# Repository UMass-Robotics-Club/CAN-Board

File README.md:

# CAN Board

Features:
* 6 CAN lines
* [RP2040](https://datasheets.raspberrypi.com/rp2040/rp2040-datasheet.pdf) microcontroller
* 16MB flash
* Many Interfaces
    * USB-C
    * UART
    * SPI
    * GPIO
* SWD debugging

This board has 6 independent CAN lines driven by 6 [MCP251863T-E/9PX](https://ww1.microchip.com/downloads/aemDocuments/documents/APID/ProductDocuments/DataSheets/MCP251863-External-CAN-FD-Controller-with-Integrated-Transceiver-DS20006624.pdf) CAN controllers. Each CAN controller is interfaced with the central microcontroller through an internal SPI bus along with 2 interrupt pins for general purpose and RX interrupts. There is also a STBY pin for the CAN transceiver that is connected to the XSTBY pin on the CAN controller.

## RP2040 Pinout
| GPIO | Function |
|------|----------|
| 0 | UART TX | 
| 1 | UART RX |
| 2 | SPI0 SCK |
| 3 | SPI0 TX |
| 4 | SPI0 RX |
| 5 | SPI0 CS 1 |
| 6 | SPI0 CS 2 |
| 7 | SPI0 CS 3 |
| 8 | SPI0 CS 4 |
| 9 | SPI0 CS 5 |
| 10 | SPI0 CS 6 |
| 11 | SPI1 TX |
| 12 | SPI1 RX |
| 13 | SPI1 CS |
| 14 | SPI1 SCK |
| 15 | GPIO pin 1 |
| 16 | CAN6 RX INT |
| 17 | CAN6 INT |
| 18 | CAN5 RX INT |
| 19 | CAN5 INT |
| 20 | CAN4 RX INT |
| 21 | CAN4 INT |
| 22 | CAN3 RX INT |
| 23 | CAN3 INT |
| 24 | CAN2 RX INT |
| 25 | CAN2 INT |
| 26 | GPIO pin 2 |
| 27 | GPIO pin 3 |
| 28 | CAN1 RX INT |
| 29 | CAN1 INT |

Notes:
* `SPI0` is the internal SPI bus which connects to the CAN controllers with `SPI0 CS X` being the chip select for CAN controller X.
* `SPI1` is the SPI bus exposed over the SPI connector.
* `GPIO 15 (GPIO pin 1)` is attached to a mosfet and LED as an indicator and therefore should have pull down enabled if being used as an input.
* `GPIO 26 & 27 (GPIO pin 26 & 27)` can be used an analog inputs.
* `CANX INT` is a general purpose interrupt pin for CAN controller X that will trigger when any interrupt in the CAN controller is triggered. This pin is inverted (active LOW).
* `CANX RX INT` is configurable to trigger when CAN controller X's RX interrupt is triggered. As an interrupt, this pin is inverted (active LOW).

## Project Structure
* `CAD`: The kiCAD project (PCB/schematics)
    * `Components`: Imported components each in their own folder
* `code`: Firmware for the microcontroller in a pretty standard C project structure
    * `include`: Header files
    * `src`: C/C++ files
* `images`: All the images

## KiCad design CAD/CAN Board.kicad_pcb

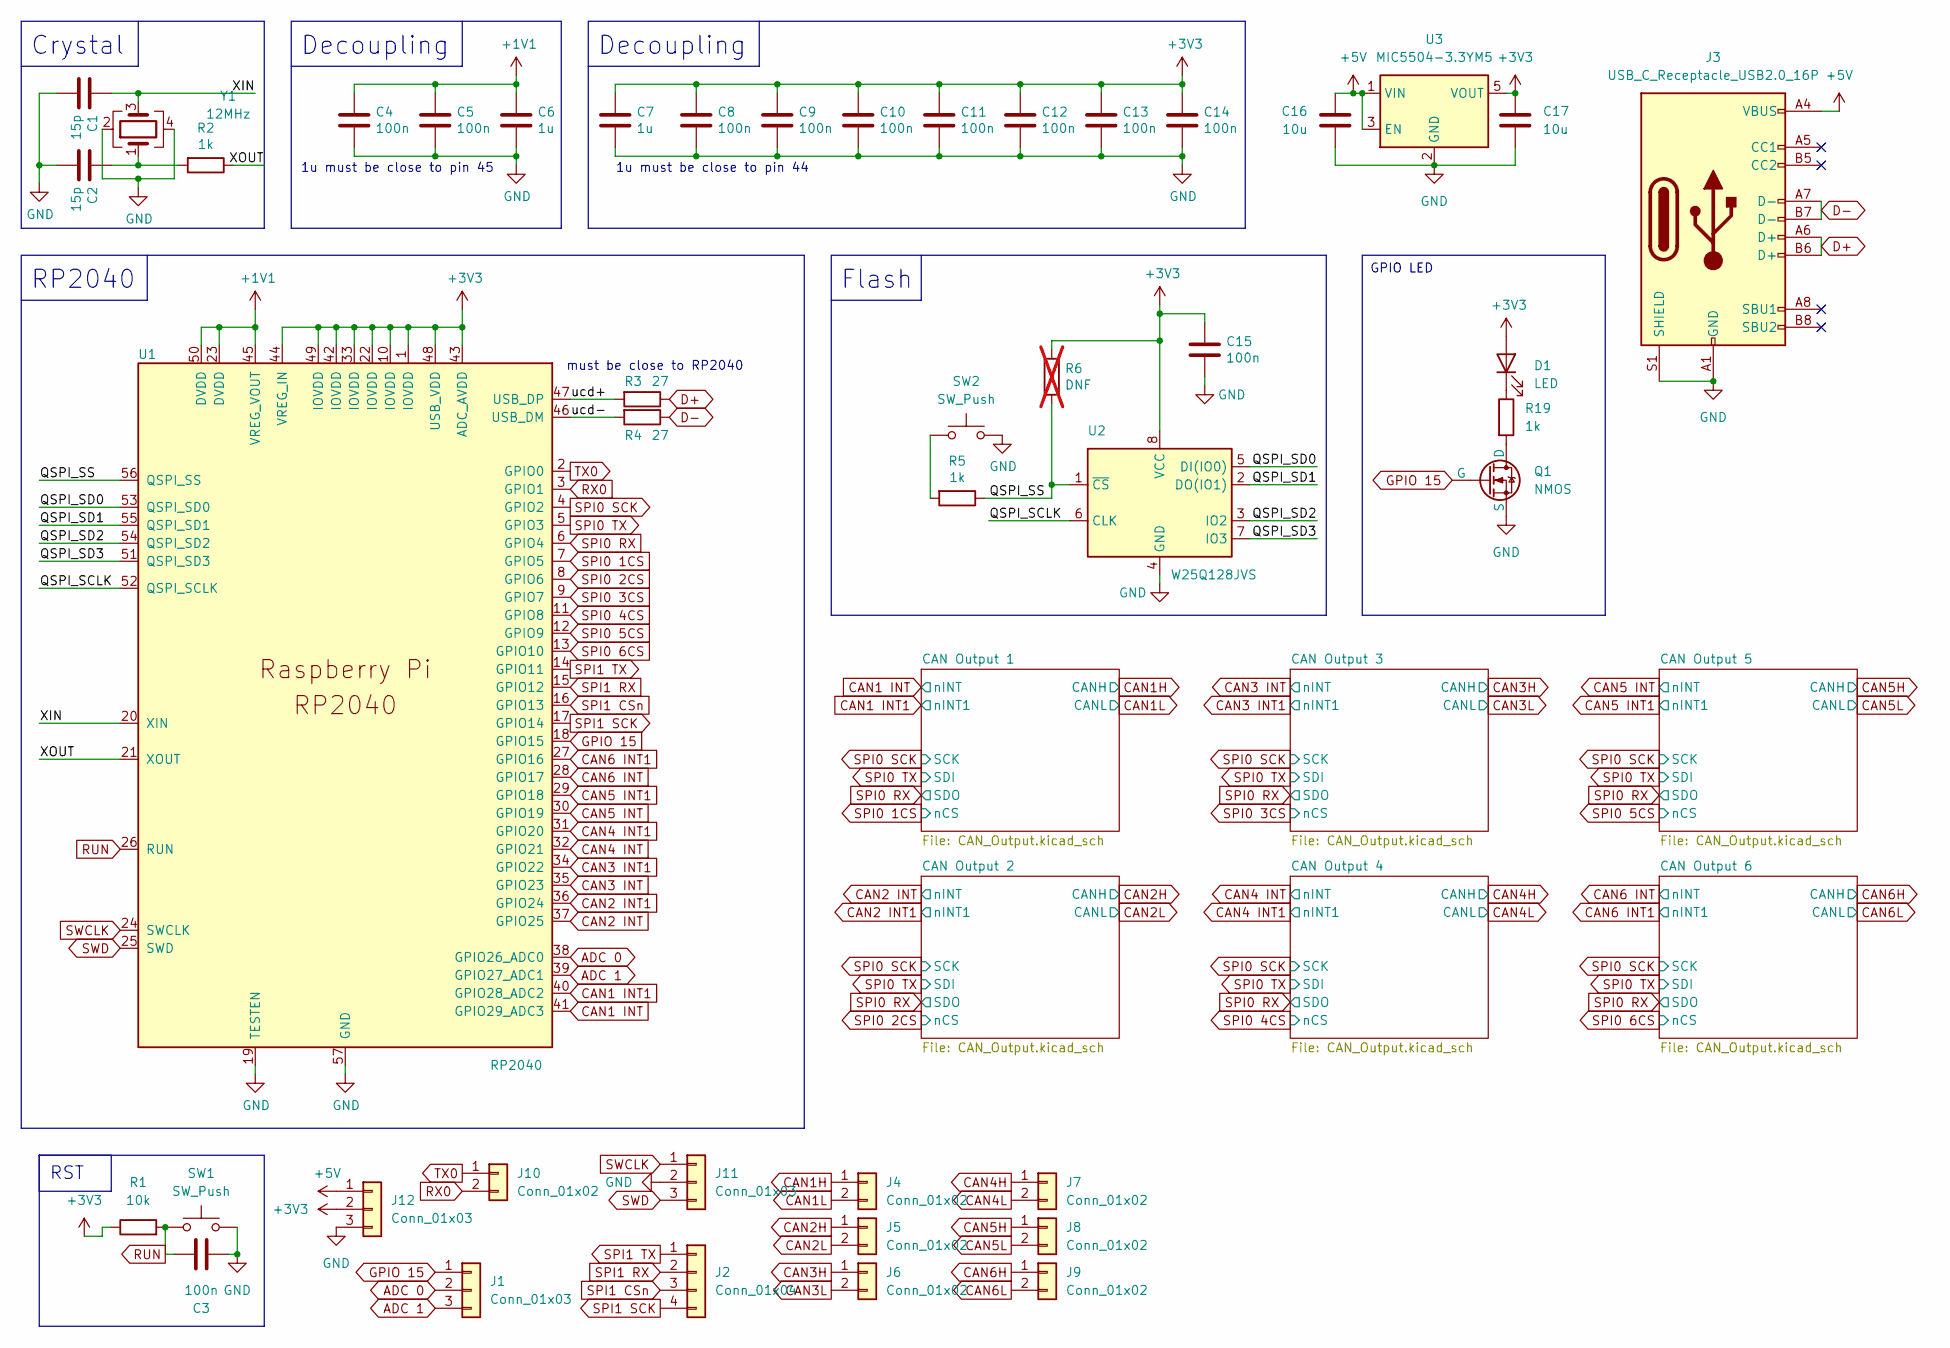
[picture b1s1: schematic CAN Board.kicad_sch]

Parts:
C1, C2: 15p; C_0603_1608Metric
C3, C4, C5, C8, C9, C10, C11, C12, C13, C14, C15: 100n; C_0603_1608Metric
C6, C7: 1u; C_0603_1608Metric
C16, C17: 10u; C_0603_1608Metric
D1: LED; LED_0603_1608Metric_Pad1.05x0.95mm_HandSolder
J1, J11, J12: Conn_01x03; Molex_PicoBlade_53047-0310_1x03_P1.25mm_Vertical
J2: Conn_01x04; Molex_PicoBlade_53047-0410_1x04_P1.25mm_Vertical
J3: USB_C_Receptacle_USB2.0_16P; USB_C_Receptacle_GCT_USB4105-xx-A_16P_TopMnt_Horizontal
J4, J5, J6, J7, J8, J9: Conn_01x02; PinSocket_1x02_P2.54mm_Vertical
J10: Conn_01x02; Molex_PicoBlade_53047-0210_1x02_P1.25mm_Vertical
Q1: NMOS; SOT-323_SC-70
R1: 10k; R_0603_1608Metric
R2, R5, R19: 1k; R_0603_1608Metric
R3, R4: 27; R_0603_1608Metric
R6: DNF; R_0603_1608Metric; not fitted
SW1, SW2: SW_Push; SW_PUSH_1P1T_6x3.5mm_H5.0_APEM_MJTP1250
U1: RP2040; QFN-56-1EP_7x7mm_P0.4mm_EP3.2x3.2mm
U2: W25Q128JVS; SOIC-8_5.23x5.23mm_P1.27mm
U3: MIC5504-3.3YM5; SOT-23-5
Y1: 12MHz; Crystal_SMD_3225-4Pin_3.2x2.5mm

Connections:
+1V1: C4.1, C5.1, C6.1, U1.23 (DVDD), U1.45 (VREG_VOUT), U1.50 (DVDD)
+3V3: C7.1, C8.1, C9.1, C10.1, C11.1, C12.1, C13.1, C14.1, C15.1, C17.1, D1.2 (A), J12.2, R1.1, R6.1, U1.1 (IOVDD), U1.10 (IOVDD), U1.22 (IOVDD), U1.33 (IOVDD), U1.42 (IOVDD), U1.43 (ADC_AVDD), U1.44 (VREG_IN), U1.48 (USB_VDD), U1.49 (IOVDD), U2.8 (VCC), U3.5 (VOUT); also elsewhere on the board
+5V: C16.1, J3.A4 (VBUS), J3.A9 (VBUS), J3.B4 (VBUS), J3.B9 (VBUS), J12.1, U3.1 (VIN), U3.3 (EN); also elsewhere on the board
/QSPI_SCLK: U1.52 (QSPI_SCLK), U2.6 (CLK)
/QSPI_SD0: U1.53 (QSPI_SD0), U2.5 (DI(IO0))
/QSPI_SD1: U1.55 (QSPI_SD1), U2.2 (DO(IO1))
/QSPI_SD2: U1.54 (QSPI_SD2), U2.3 (IO2)
/QSPI_SD3: U1.51 (QSPI_SD3), U2.7 (IO3)
/QSPI_SS: R5.1, R6.2, U1.56 (QSPI_SS), U2.1 (~CS)
/XIN: C1.1, U1.20 (XIN), Y1.3
/XOUT: R2.1, U1.21 (XOUT)
/ucd+: R3.2, U1.47 (USB_DP)
/ucd-: R4.2, U1.46 (USB_DM)
ADC 0: J1.2, U1.38 (GPIO26_ADC0)
ADC 1: J1.3, U1.39 (GPIO27_ADC1)
CAN1 INT: U1.41 (GPIO29_ADC3); also elsewhere on the board
CAN1 INT1: U1.40 (GPIO28_ADC2); also elsewhere on the board
CAN1H: J4.1; also elsewhere on the board
CAN1L: J4.2; also elsewhere on the board
CAN2 INT: U1.37 (GPIO25); also elsewhere on the board
CAN2 INT1: U1.36 (GPIO24); also elsewhere on the board
CAN2H: J5.1; also elsewhere on the board
CAN2L: J5.2; also elsewhere on the board
CAN3 INT: U1.35 (GPIO23); also elsewhere on the board
CAN3 INT1: U1.34 (GPIO22); also elsewhere on the board
CAN3H: J6.1; also elsewhere on the board
CAN3L: J6.2; also elsewhere on the board
CAN4 INT: U1.32 (GPIO21); also elsewhere on the board
CAN4 INT1: U1.31 (GPIO20); also elsewhere on the board
CAN4H: J7.1; also elsewhere on the board
CAN4L: J7.2; also elsewhere on the board
CAN5 INT: U1.30 (GPIO19); also elsewhere on the board
CAN5 INT1: U1.29 (GPIO18); also elsewhere on the board
CAN5H: J8.1; also elsewhere on the board
CAN5L: J8.2; also elsewhere on the board
CAN6 INT: U1.28 (GPIO17); also elsewhere on the board
CAN6 INT1: U1.27 (GPIO16); also elsewhere on the board
CAN6H: J9.1; also elsewhere on the board
CAN6L: J9.2; also elsewhere on the board
D+: J3.A6 (D+), J3.B6 (D+), R3.1
D-: J3.A7 (D-), J3.B7 (D-), R4.1
GND: C1.2, C2.2, C3.2, C4.2, C5.2, C6.2, C7.2, C8.2, C9.2, C10.2, C11.2, C12.2, C13.2, C14.2, C15.2, C16.2, C17.2, J3.A1 (GND), J3.A12 (GND), J3.B1 (GND), J3.B12 (GND), J3.S1 (SHIELD), J11.2, J12.3, Q1.3 (S), SW1.2, SW2.2, U1.19 (TESTEN), U1.57 (GND), U2.4 (GND), U3.2 (GND), Y1.2, Y1.4; also elsewhere on the board
GPIO 15: J1.1, Q1.2 (G), U1.18 (GPIO15)
unnamed: C2.1, R2.2, Y1.1
unnamed: D1.1 (K), R19.1
unnamed: Q1.1 (D), R19.2
unnamed: R5.2, SW2.1
RUN: C3.1, R1.2, SW1.1, U1.26 (RUN)
RX0: J10.2, U1.3 (GPIO1)
SPI0 1CS: U1.7 (GPIO5); also elsewhere on the board
SPI0 2CS: U1.8 (GPIO6); also elsewhere on the board
SPI0 3CS: U1.9 (GPIO7); also elsewhere on the board
SPI0 4CS: U1.11 (GPIO8); also elsewhere on the board
SPI0 5CS: U1.12 (GPIO9); also elsewhere on the board
SPI0 6CS: U1.13 (GPIO10); also elsewhere on the board
SPI0 RX: U1.6 (GPIO4); also elsewhere on the board
SPI0 SCK: U1.4 (GPIO2); also elsewhere on the board
SPI0 TX: U1.5 (GPIO3); also elsewhere on the board
SPI1 CSn: J2.3, U1.16 (GPIO13)
SPI1 RX: J2.2, U1.15 (GPIO12)
SPI1 SCK: J2.4, U1.17 (GPIO14)
SPI1 TX: J2.1, U1.14 (GPIO11)
SWCLK: J11.1, U1.24 (SWCLK)
SWD: J11.3, U1.25 (SWD)
TX0: J10.1, U1.2 (GPIO0)

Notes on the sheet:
GPIO LED
RST
Crystal
RP2040
Decoupling
Flash
must be close to RP2040
1u must be close to pin 45
1u must be close to pin 44

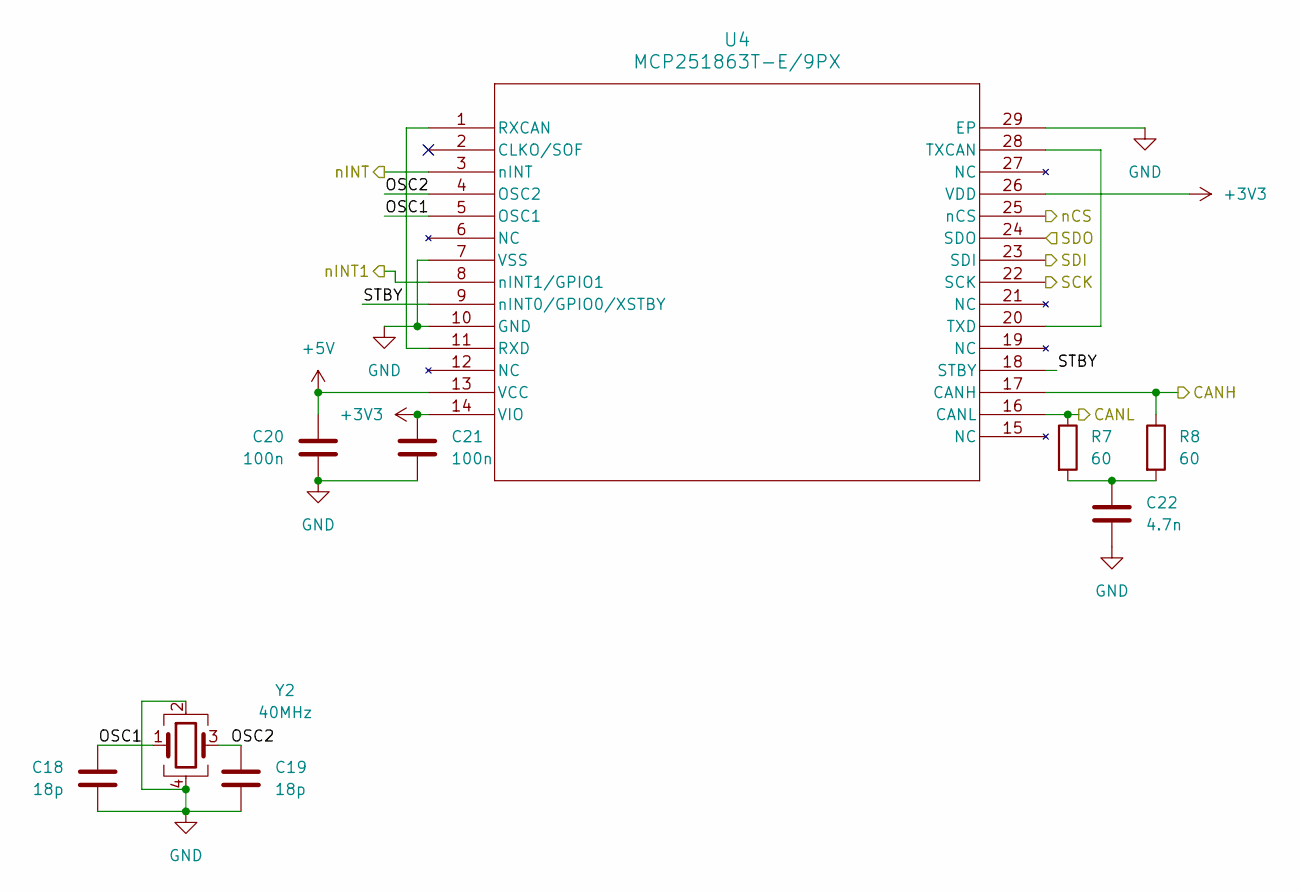
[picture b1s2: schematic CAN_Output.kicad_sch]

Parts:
C18, C19: 18p; C_0603_1608Metric
C20, C21: 100n; C_0603_1608Metric
C22: 4.7n; C_0603_1608Metric
R7, R8: 60; R_0603_1608Metric
U4: MCP251863T-E/9PX; VQFN28_9PX_3p25X3p25EPAD_MCH
Y2: 40MHz; Crystal_SMD_3225-4Pin_3.2x2.5mm

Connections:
+3V3: C21.1, U4.14 (VIO), U4.26 (VDD); also elsewhere on the board
+5V: C20.1, U4.13 (VCC); also elsewhere on the board
/CAN Output 1/OSC1: C18.1, U4.5 (OSC1), Y2.1
/CAN Output 1/OSC2: C19.1, U4.4 (OSC2), Y2.3
/CAN Output 1/STBY: U4.9 (nINT0/GPIO0/XSTBY), U4.18 (STBY)
CAN1 INT: U4.3 (nINT); also elsewhere on the board
CAN1 INT1: U4.8 (nINT1/GPIO1); also elsewhere on the board
CAN1H: R8.1, U4.17 (CANH); also elsewhere on the board
CAN1L: R7.1, U4.16 (CANL); also elsewhere on the board
GND: C18.2, C19.2, C20.2, C21.2, C22.2, U4.7 (VSS), U4.10 (GND), U4.29 (EP), Y2.2, Y2.4; also elsewhere on the board
unnamed: C22.1, R7.2, R8.2
unnamed: U4.1 (RXCAN), U4.11 (RXD)
unnamed: U4.20 (TXD), U4.28 (TXCAN)
SPI0 1CS: U4.25 (nCS); also elsewhere on the board
SPI0 RX: U4.24 (SDO); also elsewhere on the board
SPI0 SCK: U4.22 (SCK); also elsewhere on the board
SPI0 TX: U4.23 (SDI); also elsewhere on the board

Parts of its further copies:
C25, C26, C32, C33, C39, C40, C46, C47, C53, C54: 18p; C_0603_1608Metric
C27, C28, C34, C35, C41, C42, C48, C49, C55, C56: 100n; C_0603_1608Metric
C29, C36, C43, C50, C57: 4.7n; C_0603_1608Metric
R9, R10, R11, R12, R13, R14, R15, R16, R17, R18: 60; R_0603_1608Metric
U5, U6, U7, U8, U9: MCP251863T-E/9PX; VQFN28_9PX_3p25X3p25EPAD_MCH
Y3, Y4, Y5, Y6, Y7: 40MHz; Crystal_SMD_3225-4Pin_3.2x2.5mm

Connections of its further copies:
+3V3: C28.1, C35.1, C42.1, C49.1, C56.1, U5.14 (VIO), U5.26 (VDD), U6.14 (VIO), U6.26 (VDD), U7.14 (VIO), U7.26 (VDD), U8.14 (VIO), U8.26 (VDD), U9.14 (VIO), U9.26 (VDD); also elsewhere on the board
+5V: C27.1, C34.1, C41.1, C48.1, C55.1, U5.13 (VCC), U6.13 (VCC), U7.13 (VCC), U8.13 (VCC), U9.13 (VCC); also elsewhere on the board
/CAN Output 2/OSC1: C25.1, U5.5 (OSC1), Y3.1
/CAN Output 2/OSC2: C26.1, U5.4 (OSC2), Y3.3
/CAN Output 2/STBY: U5.9 (nINT0/GPIO0/XSTBY), U5.18 (STBY)
/CAN Output 3/OSC1: C32.1, U6.5 (OSC1), Y4.1
/CAN Output 3/OSC2: C33.1, U6.4 (OSC2), Y4.3
/CAN Output 3/STBY: U6.9 (nINT0/GPIO0/XSTBY), U6.18 (STBY)
/CAN Output 4/OSC1: C39.1, U7.5 (OSC1), Y5.1
/CAN Output 4/OSC2: C40.1, U7.4 (OSC2), Y5.3
/CAN Output 4/STBY: U7.9 (nINT0/GPIO0/XSTBY), U7.18 (STBY)
/CAN Output 5/OSC1: C46.1, U8.5 (OSC1), Y6.1
/CAN Output 5/OSC2: C47.1, U8.4 (OSC2), Y6.3
/CAN Output 5/STBY: U8.9 (nINT0/GPIO0/XSTBY), U8.18 (STBY)
/CAN Output 6/OSC1: C53.1, U9.5 (OSC1), Y7.1
/CAN Output 6/OSC2: C54.1, U9.4 (OSC2), Y7.3
/CAN Output 6/STBY: U9.9 (nINT0/GPIO0/XSTBY), U9.18 (STBY)
CAN2 INT: U5.3 (nINT); also elsewhere on the board
CAN2 INT1: U5.8 (nINT1/GPIO1); also elsewhere on the board
CAN2H: R10.1, U5.17 (CANH); also elsewhere on the board
CAN2L: R9.1, U5.16 (CANL); also elsewhere on the board
CAN3 INT: U6.3 (nINT); also elsewhere on the board
CAN3 INT1: U6.8 (nINT1/GPIO1); also elsewhere on the board
CAN3H: R12.1, U6.17 (CANH); also elsewhere on the board
CAN3L: R11.1, U6.16 (CANL); also elsewhere on the board
CAN4 INT: U7.3 (nINT); also elsewhere on the board
CAN4 INT1: U7.8 (nINT1/GPIO1); also elsewhere on the board
CAN4H: R14.1, U7.17 (CANH); also elsewhere on the board
CAN4L: R13.1, U7.16 (CANL); also elsewhere on the board
CAN5 INT: U8.3 (nINT); also elsewhere on the board
CAN5 INT1: U8.8 (nINT1/GPIO1); also elsewhere on the board
CAN5H: R16.1, U8.17 (CANH); also elsewhere on the board
CAN5L: R15.1, U8.16 (CANL); also elsewhere on the board
CAN6 INT: U9.3 (nINT); also elsewhere on the board
CAN6 INT1: U9.8 (nINT1/GPIO1); also elsewhere on the board
CAN6H: R18.1, U9.17 (CANH); also elsewhere on the board
CAN6L: R17.1, U9.16 (CANL); also elsewhere on the board
GND: C25.2, C26.2, C27.2, C28.2, C29.2, C32.2, C33.2, C34.2, C35.2, C36.2, C39.2, C40.2, C41.2, C42.2, C43.2, C46.2, C47.2, C48.2, C49.2, C50.2, C53.2, C54.2, C55.2, C56.2, C57.2, U5.7 (VSS), U5.10 (GND), U5.29 (EP), U6.7 (VSS), U6.10 (GND), U6.29 (EP), U7.7 (VSS), U7.10 (GND), U7.29 (EP), U8.7 (VSS), U8.10 (GND), U8.29 (EP), U9.7 (VSS), U9.10 (GND), U9.29 (EP), Y3.2, Y3.4, Y4.2, Y4.4, Y5.2, Y5.4, Y6.2, Y6.4, Y7.2, Y7.4; also elsewhere on the board
unnamed: C29.1, R9.2, R10.2
unnamed: C36.1, R11.2, R12.2
unnamed: C43.1, R13.2, R14.2
unnamed: C50.1, R15.2, R16.2
unnamed: C57.1, R17.2, R18.2
unnamed: U5.1 (RXCAN), U5.11 (RXD)
unnamed: U5.20 (TXD), U5.28 (TXCAN)
unnamed: U6.1 (RXCAN), U6.11 (RXD)
unnamed: U6.20 (TXD), U6.28 (TXCAN)
unnamed: U7.1 (RXCAN), U7.11 (RXD)
unnamed: U7.20 (TXD), U7.28 (TXCAN)
unnamed: U8.1 (RXCAN), U8.11 (RXD)
unnamed: U8.20 (TXD), U8.28 (TXCAN)
unnamed: U9.1 (RXCAN), U9.11 (RXD)
unnamed: U9.20 (TXD), U9.28 (TXCAN)
SPI0 2CS: U5.25 (nCS); also elsewhere on the board
SPI0 3CS: U6.25 (nCS); also elsewhere on the board
SPI0 4CS: U7.25 (nCS); also elsewhere on the board
SPI0 5CS: U8.25 (nCS); also elsewhere on the board
SPI0 6CS: U9.25 (nCS); also elsewhere on the board
SPI0 RX: U5.24 (SDO), U6.24 (SDO), U7.24 (SDO), U8.24 (SDO), U9.24 (SDO); also elsewhere on the board
SPI0 SCK: U5.22 (SCK), U6.22 (SCK), U7.22 (SCK), U8.22 (SCK), U9.22 (SCK); also elsewhere on the board
SPI0 TX: U5.23 (SDI), U6.23 (SDI), U7.23 (SDI), U8.23 (SDI), U9.23 (SDI); also elsewhere on the board

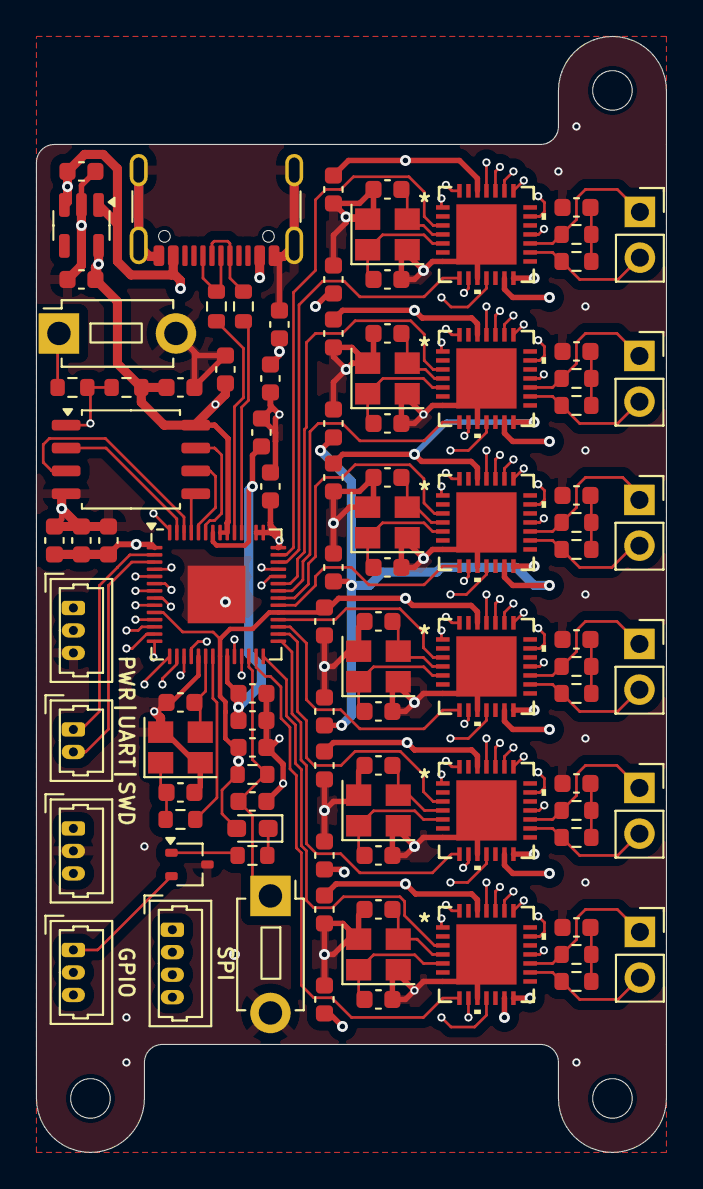
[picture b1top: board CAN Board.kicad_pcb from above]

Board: 4 copper layers, 35.0 x 62.0 mm, 98 parts (0 on the bottom side), 101 nets.

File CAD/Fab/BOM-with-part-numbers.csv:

Comment,Designator,Footprint,Qty,LCSC Part Number,Digikey Part Number,Comment
100nF,"C48,C34,C56,C11,C41,C8,C9,C13,C27,C12,C15,C42,C35,C3,C20,C49,C28,C4,C14,C5,C10,C55,C21",0603,23,C282519,2679-C0603X7R500-104KNP-CT-ND,
4.7nF,"C36,C57,C22,C29,C43,C50",0603,6,,1292-1440-1-ND,
1uF,"C7,C6",0603,2,C26413,2679-C0603X5R100-105KNE-CT-ND,
10uF,"C17,C16",0603,2,C19702,1292-0603X106M6R3CT-ND,
1k,"R19,R2,R5",0603,3,C269704,13-RC0603JR-101KLCT-ND,
60,"R12,R18,R16,R17,R14,R11,R8,R7,R9,R10,R13,R15",0603,12,,,
27,"R4,R3",0603,2,C2770847,2019-RK73B1JTTD270JCT-ND,
10k,R1,0603,1,C3017715,13-RC0603FR-7W10KLCT-ND,
MCP251863T-E/9PX,"U8,U4,U9,U7,U6,U5",VQFN28_9PX_3p25X3p25EPAD_MCH,6,C20295647,150-MCP251863T-E/9PXCT-ND,Not sure if we can use from LCSC (min order 500)
W25Q128JVS,U2,SOIC-8,1,C97521,W25Q128JVSIQ-ND,
MIC5504-3.3YM5,U3,SOT-23-5,1,C3021093,576-4764-1-ND,
RP2040,U1,QFN-56-1EP_7x7mm_P0.4mm_EP3.2x3.2mm,1,C2040,2648-SC0914(13)CT-ND,
40MHz (18p load),"Y7,Y3,Y5,Y4,Y2,Y6",SMD3225-4P,6,C1985459,535-10281-1-ND,
18pF,"C54,C33,C25,C53,C32,C40,C18,C19,C26,C39,C47,C46",0603,12,C527046,2679-C0603C0G250-180JNP-CT-ND,
12 MHz (15p load),Y1,SMD3225-4P,1,C20625731,535-ABM8-272-T3CT-ND,
15pF,"C2,C1",0603,2,C302055,1292-1487-1-ND,
NMOS,Q1,SOT-323_SC-70,1,,,
LED,D1,0603,1,,,

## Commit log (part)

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2024-11-20 added board
2024-11-20 cleaning up
2024-11-21 moving stuff
2024-11-21 moving components
2024-11-24 routed data, power lift
2024-12-05 it has no errors :)
2024-12-08 cleaning up and minor updates
2024-12-08 slight moving of parts
2024-12-08 added mounting holes
2025-01-26 updated baord
2025-01-26 added LED and cleanup
2025-01-26 updated readne
2025-01-27 added basic framework
2025-01-27 cleanup
2025-01-27 slight fix to header
2025-02-02 updated board
2025-02-02 added screw holes
2025-02-02 added part numbers
2025-02-13 added kicad zip
2025-02-14 updated silkscreen
2025-02-15 updated stby pinout
2025-02-15 finished pin config
2025-02-16 added simple code
2025-02-16 adding docs
2025-02-18 simple firmware
2025-02-21 updated CAN termination
2025-02-21 updated BOM
2025-03-02 added better readme
2025-03-17 updated code
2025-04-04 working transmit version
2025-04-06 worked on some stuff
2025-04-11 added more testing code
2025-05-04 updated to be pico project
2025-10-14 Added new directory for testing quadruped 2025
2025-10-20 Adjusted main.c for rs02 test
2025-10-20 Resolved errors and typos
2025-10-29 Edited some typos and errors
2025-11-11 Partially included functionality to get response CAN frames from motor
2025-11-14 ignore
2025-11-14 Modified CMake files after flashing to Pico
2025-12-03 restructured and recompiled code for pico 1 instead of 2
2025-12-09 SPI testing complete
2026-02-19 random update (IDK)
2026-02-19 working on new interface
2026-02-23 fully functioning CAN board!
2026-02-24 it works!!!!
2026-03-03 MIT stuff
2026-03-03 got MIT mode working
2026-03-23 mit mode + reading most recent rx event
2026-04-28 added spark max stuff
2026-04-28 updated stuff
2026-05-03 adding better input handling
